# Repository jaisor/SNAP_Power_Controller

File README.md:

# SNAP Power Controller

A small solar charger board for a single-cell (1S) Li-ion/LiPo battery, built for solar-powered LoRa mesh nodes such as [SNAP v1.2](https://makerworld.com/en/models/3360988-snap-v1-2-solar-node-adaptable-platform-2x200ma). Up to four 5V panels feed a CN3791 MPPT buck charger. A switched output powers the node, and an INA3221 reports voltage and current on three channels over I2C.

Designed in KiCad 10.

> **Status:** the schematic is complete and passes ERC. The PCB (52 × 29 mm, 2mm corner chamfers, four M3 mounting holes, two layers) is **placed and routed** with a clean DRC, but hasn't had a manual layout review. A first board has been wired up and tested with a XIAO + Wio-SX1262 on a custom Meshtastic build, and everything seems to work as expected so far, including the I2C sensor. A sunlight test in a real solar node is under way, with the expected voltage and charge current so far. See [Testing](#testing).
>
> **v1.1:** a three-channel INA3221 replaces v1.0's INA219 and its SOLAR/BATT switch, and the board is smaller. v1.1 hasn't been built or tested yet; the test results below are from v1.0 boards with the INA219. See the [change log](CHANGELOG.md).

## Built for solar mesh nodes

This controller is meant for solar mesh nodes like the [SNAP v1.2: Solar Node Adaptable Platform](https://makerworld.com/en/models/3360988-snap-v1-2-solar-node-adaptable-platform-2x200ma). It simplifies their build in three ways:

- **Easy, clean connections:** the panels, battery, node and switches each plug into their own connector.
- **Improved solar charging:** an MPPT charger tuned for 5V panels, with a diode for every panel built into the board.
- **I2C power sensing:** configurable for either the battery or the solar circuit.

I2C power sensors are supported natively by both [Meshtastic](https://meshtastic.org) and [MeshCore](https://github.com/meshcore-dev/MeshCore). In most cases the node recognizes the INA3221 automatically once it's connected.

In the SNAP v1.2 example build, shown below, the board replaces several separately wired parts:

| Example build part | With this board |
|---|---|
| CN3158 MPPT module (SDBK03TA) | CN3791 MPPT buck charger, tuned for 5V panels (VIN held at 4.42V) and charging at 0.8A |
| One 1N5819 per panel, soldered inline | A 1N5819WS per input on the board, for up to four panels |
| Hand-soldered panel, battery and node wiring | Plug-in connectors for every connection: Micro JST 1.25, with 2.54mm pin headers for the switches |
| Latching on/off switch wired into the battery lead | Two switch connectors: SW_BATT cuts the battery, SW_LOAD cuts only the node |
| (none) | INA3221 power monitor on I2C, reading the battery, the total solar input and panel 1 at once |

### Example wiring

| Board connector | Connects to |
|---|---|
| J1, J2 (Solar_5V) | Two [FellDen 5V 200mA 110×60mm panels](https://www.amazon.com/dp/B0BND5NYGK), the ones SNAP v1.2 uses. J3 and J4 take up to two more |
| J5 (BATT) | An 18650 Li-ion cell (1S, 3.0–4.2V) in its holder |
| J8 (SW_LOAD) | The SNAP on/off switch cap's latching button. To cut the battery entirely, use J7 (SW_BATT) as well, or instead |
| J7 / J8 left unswitched | Both switch connectors are in series with the power path, so an unused one needs a 2.54mm jumper cap, or a wire bridging its pads on the back of the board. Otherwise the battery or the node stays disconnected |
| J6 (VOUT) | The XIAO nRF52840's BAT+ / BAT− pads, which is where SNAP powers it from the 18650 today |
| J9 (I2C) | XIAO 3V3 → VCC, D6 → SDA, D7 → SCL, GND → GND, on a 4-wire cable coloured red VCC, black GND, yellow SCL, white SDA. These pins need a Meshtastic build with I2C on D6/D7 (see the table below) |
| JP1 (LED) | Nothing. Bridge it with solder if you want the status LEDs. It's open as supplied, so the LEDs stay dark |

The INA3221 reads the battery's charge and discharge current, what the panels deliver in total, and panel 1 on its own, all at the same time. There's no switch to set.

The XIAO's I2C pins depend on the firmware build. D4 and D5 can't be used with the Wio-SX1262, because the radio uses them.

| Firmware build | SDA | SCL | Status |
|---|---|---|---|
| Meshtastic `seeed_xiao_nrf52840_kit`, custom build with I2C on D6/D7 | D6 | D7 | Tested on this board |
| Meshtastic `seeed_xiao_nrf52840_kit_i2c` | D6 | D7 | From the firmware source, not tested |
| Meshtastic `seeed_xiao_nrf52840_kit`, unmodified (D6/D7 are reserved for the GNSS module) | NFC1 pad (underside) | NFC2 pad (underside) | From the firmware source, not tested |
| MeshCore `Xiao_nrf52` | D7 | D6 | From the firmware source, not tested |

The INA3221 uses address 0x42. Meshtastic also expects the DFRobot Lark weather sensor at 0x42, so the two can't share a bus.

In Meshtastic, enable power metrics in the telemetry settings so the readings are sent to the mesh.

## Features

- **Solar input:** up to four 5V panels in parallel (Micro JST 1.25), each isolated by its own 1N5819WS Schottky (SOD-323) so a shaded or unplugged panel doesn't drag the others down.
- **MPPT charging:** [CN3791](https://naylampmechatronics.com/img/cms/001216/CN3791.PDF) PWM buck charger with constant-voltage MPPT set to 4.42V input. Charges at 0.8A to 4.2V (CC/CV, trickle charge for deeply discharged cells, automatic recharge).
- **Battery and load switching:** connectors for two panel-mount switches. **SW_BATT** disconnects the battery from everything. **SW_LOAD** cuts only the output, so the battery keeps charging.
- **Output:** VOUT connector (Micro JST 1.25) that powers the module from the battery.
- **Reverse-battery protection:** Q2, a P-channel MOSFET between the battery connector and the rest of the board. A cell plugged in backwards is blocked instead of shorting through the charger. With the cell the right way round, Q2 is fully on in both directions, adding about 60mV of drop at 0.8A.
- **Power monitoring:** [INA3221](https://www.ti.com/lit/ds/symlink/ina3221.pdf) at I2C address 0x42, with three channels: the battery (bidirectional current plus voltage), the total solar input, and panel 1 on its own.
- **Status LEDs:** red while charging, green when charging is done. They're powered through JP1, an open solder jumper next to R1 on the top of the board: bridge its two pads with solder to turn them on. Left open, the LEDs are disconnected and draw nothing.

## Schematic

The schematic follows the CN3791 datasheet's typical application circuit (Figure 1), with these changes:

| Item | Value | Why |
|---|---|---|
| Charge current | 0.8A (R5 = 0.15Ω) | I<sub>CH</sub> = 120mV / R5. Leaves margin on the 1.0A-rated connectors; use 0.24Ω for 0.5A with small cells. |
| MPPT setpoint | 4.42V at VIN (R3/R4 = 26.7k/10k) | Chosen for panels that measure about 5.5V open-circuit. It's below the CN3791's specified 4.5V minimum input. Typical parts run down to their 3.8V undervoltage lockout, but the datasheet doesn't guarantee it. With 6V panels, use R3 = 30.1k (4.83V), which stays in spec. V<sub>MPPT</sub> = 1.205V × (1 + R3/R4). The panels sit one diode drop higher (~4.7–4.9V), a little under a cool 5V panel's max-power voltage of about 5.0V. That voltage falls about 0.4% per °C, to about 4.2V at a 65°C cell temperature, and a fixed set point above it cuts the panel's output. Modeled for a 10-cell panel, 4.42V gives 99% of maximum power at 25°C and 84% at 65°C. v1.0's 4.58V (28.0k) gives 100% and 71%. |
| Blocking diode D1 | omitted | The input diodes already stop the battery feeding back into the panels. Leaving D1 out saves ~0.4V of headroom; the trade-off is ~21µA of battery drain in the dark. |
| Inductor | 22µH, Bourns SRN6045TA | Meets the datasheet's L > 5 × (VCC − VBAT) µH, with ~0.2A ripple. |
| Input diodes | 1N5819WS, SOD-323 (40V/1A) | The panels peak at ~200–300mA each, so the SMD part has plenty of margin and saves ~12mm of board width over DO-41. |

## PCB

| Area | Parts |
|---|---|
| Left end | M3 mounting holes H1/H3 in the corners. Between them, the 4-pin I2C connector J9 at the edge and the INA3221 (U2) beside it, with its bypass capacitor C6 and the I2C pull-ups R8/R9 above |
| Left column | Solar inputs J1–J4, each with its 1N5819WS (D5–D8). Panel 1's shunt R10 sits beside J1, with D5 just below it |
| Top middle | Buck power stage in current-flow order: R7, C1/C5, Q1, D2, L1, R5, C3 |
| Middle | CN3791 (U1) with its support parts and status LEDs, and JP1, the LED solder jumper, right of R1 |
| Right middle | Under L1: battery shunt R6 and reverse-battery MOSFET Q2, then VOUT (J6) and battery (J5) |
| Right end | M3 mounting holes H2/H4 in the corners, with the SW_BATT/SW_LOAD switch headers (J7/J8) between them |

Every reference label sits next to its own part, clear of pads, other parts and the edge (DRC reports no silkscreen issues). The holes are plain non-plated 3.2mm M3 holes, 4mm in from each edge.

### Dimensions

The [wiring diagram](#built-for-solar-mesh-nodes) includes a dimension drawing to scale.

| | |
|---|---|
| Outline | 52 × 29mm, with a 2mm × 45° chamfer on each corner |
| Thickness | 1.6mm PCB, two layers. All parts are on the top side; the through-hole connector pins stick out the back |
| Mounting holes | Four, 3.2mm diameter, not plated, for M3 screws |
| Hole positions | One in each corner, centre 4mm from both edges |
| Hole spacing | 44mm across, 21mm down, centre to centre |

**Silkscreen labels:**

- **Connector functions:** `SW_BATT` (J7) and `SW_LOAD` (J8) are printed above the two switch headers. `BATT` (J5) and `VOUT` (J6) are vertical labels to the left of those connectors.
- **Solar inputs:** one `Solar_5V` label, with a bracket along the four solar inputs (J1–J4).
- **Polarity:** `-` and `+` under the solar, battery and VOUT connectors (J1–J6), on the side of the matching pin.
- **I2C connector:** `I2C` under J9 on the front (J9 has no reference label; there's no room for both). The pin names (`VCC`, `GND`, `SCL`, `SDA`) are printed beside its pads on the back.
- **Back:** the module ID, "Solar Charge Module v1.1 / by JaisorGadgets / Nov. 9, 2026".

**Routing** (drawn by hand in `tools/draw-routes.py`, so it comes out the same on every run):

- **Ground:** the bottom layer is a GND plane in one piece, covering about 87% of the board, and the top layer has a GND fill. Every surface-mount GND pad gets its own via down to the plane, and 46 stitching vias on a 3mm grid tie the two pours together.
- **Track widths:** power paths are 0.8mm, 0.4mm into the small diode pads. Signals are 0.25mm, with 0.2mm on the sense lines where they squeeze past pads.
- **Kelvin sensing:** the CN3791's current-sense pins and each INA3221 channel's two inputs connect straight to the pads of their shunt resistors (R5; R6, R7, R10). Each channel's two sense lines run side by side. Channel 3's pair runs over and under J1, channel 2's passes between J2 and J3, and channel 1's follows the bottom edge from the battery shunt to U2.
- **Layer use:** nearly all track is on the top layer: about 454mm, against 25mm on the bottom. The bottom layer only carries short hops: the gate drive under VIN, VIN to R3, the two channel 2 sense lines under the PV bus, and three links under U2.
- **Size:** 212 track segments and 68 vias, 57 of them on GND.
- **Checks:** DRC reports 0 violations and 0 unconnected items, and schematic parity is clean.

Review it before ordering, especially the buck converter's switching loop (C1 → Q1 → D2, which returns through the ground plane).

Still to do: a manual layout review before ordering (see Fabrication).

## Connectors

| Ref | Connector | Pin 1 | Pin 2 | Notes |
|---|---|---|---|---|
| J1–J4 | Micro JST 1.25, 2-pin | Panel + | GND | 5V solar panels, any combination of 1–4 |
| J5 | Micro JST 1.25, 2-pin | Battery + | GND | 1S Li-ion/LiPo, 4.2V |
| J6 | Micro JST 1.25, 2-pin | VOUT | GND | Battery voltage out to the powered module, through SW_LOAD |
| J7 | 2.54mm pin header, 2-pin | VBAT (charger) | BATT+ (battery) | SW_BATT: panel-mount SPST switch, rated ≥1A or the module's peak current |
| J8 | 2.54mm pin header, 2-pin | VBAT | VOUT | SW_LOAD: panel-mount SPST switch, same rating |
| J9 | Micro JST 1.25, 4-pin | VCC (3.3–5V) | GND | Pin 3 = SCL, pin 4 = SDA, matching the common red/black/yellow/white 4-wire cable. VCC comes from the MCU and powers the INA3221. v1.0 boards have SDA on pin 2 and GND on pin 4. |

J1–J6 and J9 are Micro JST 1.25 (Molex PicoBlade-compatible) vertical headers, Molex 53047-0210 (2-pin) and 53047-0410 (4-pin). They mate with standard female cable housings (Molex 51021). J7 and J8 are standard 2.54mm vertical pin headers, which take a 2.54mm female housing or a jumper cap. Notes:

- **Current:** PicoBlade contacts are rated 1.0A. The charge current is set to 0.8A to stay under that on the battery connector (J5). Keep the module's load current under 1A too, since it flows through J5 when the panels are dark.
- **No keying between functions:** J1–J6 are the same 2-pin type, so a battery lead fits a solar socket. Check the silkscreen before plugging in. The switch headers take a different plug, so they can't be mixed up with these.
- **Battery polarity:** "JST 1.25" LiPo pigtails have no standard polarity. Check that red goes to the pin marked `+` (pin 1 on J5) before connecting. Q2 blocks a reversed cell, but fit the cell with SW_BATT off anyway: with SW_BATT on in sunlight, the charger's output can partly turn Q2 on and push a limited current into a reversed cell, which heats Q2.
- **Reading the marks:** pin 1 is `+` on J1–J6. J1–J4 are rotated 180° from J5 and J6, so the marks read `- J1 +` on the solar inputs and `+ J5 -` on the right-hand connectors.

**Operating note:** if SW_BATT is off while the panels are in sun, the charger sees no battery and VBAT pulses around 4.2V. Keep SW_LOAD off in that state.

## Power monitor (INA3221)

- **Address:** 0x42 (A0 = SDA). That's the INA3221 default in both Meshtastic and MeshCore.
- **Shunts:** all three are 0.1Ω, which both firmwares assume. Full scale is ±163.8mV, so about ±1.64A, in 0.4mA steps.
- **Pull-ups:** R8/R9 are 10k I2C pull-ups to the MCU's VCC. Leave them off if the MCU board already has pull-ups.

| Channel | Shunt | Current | Bus voltage |
|---|---|---|---|
| 1 | R6, between BATT+ and the cell | Positive while charging, negative while discharging | Cell voltage, readable even with SW_BATT off. It's measured after Q2, so it reads up to about 50mV off while current flows |
| 2 | R7, between the PV bus and VIN | Total solar current, always ≥ 0 | VIN (panel voltage minus the diode drop) |
| 3 | R10, between J1 and its diode D5 | Panel 1's current, always ≥ 0 | Panel 1's own voltage, before its diode |

Channel 3 shows where panel 1 actually operates, which is the number to compare against the panel's maximum-power voltage when tuning the MPPT set point.

**Firmware support** (checked in the source code on 2026-11-09, not yet on hardware):
- **Meshtastic:** looks for an INA3221 at 0x42. It reports all three channels' voltage and current as power metrics, and uses channel 1 as the battery by default.
- **MeshCore:** the XIAO nRF52 build includes INA3221 support (`ENV_INCLUDE_INA3221`). It reports voltage, current and power for each channel.

## Testing

| Test | Setup | Status |
|---|---|---|
| First power-up | Board wired to a XIAO + Wio-SX1262, running Meshtastic built from `seeed_xiao_nrf52840_kit` with I2C on D6/D7 | Done. Everything seems to work as expected, including the INA219 over I2C |
| INA219 battery current | Same setup, battery at about 4V | Done. Discharging: about −12 to −15mA. Charging from the XIAO's USB: +100mA |
| Sunlight | Board wired into a real solar node with 4 × 60mA panels, with metrics tracked in Grafana dashboards | In progress. Voltage and charge current rose as expected when exposed to sunlight. One reading in the Meshtastic app: 4.56V, 110.5mA |

The signs match the expected convention: positive while charging, negative while discharging. The USB reading comes from the XIAO's own charger, so it doesn't test the CN3791. The sunlight reading is from SW3's SOLAR position: 4.56V is above a Li-ion cell's 4.2V and close to the 4.58V MPPT set point of the board tested (v1.1 lowers it to 4.42V). It's a single reading, and longer-term results are still to come. These tests used a board with Micro JST 1.25 connectors on J7 and J8, so the pin-header version hasn't been built yet. In the sunlight test build, J7 and J8 are bridged with wire on the back of the board, so neither switch is fitted.

## Safety

This is an experimental design for charging a lithium-ion cell. It's provided as is, with no warranty, and hasn't been certified to any safety standard. If you build it, you're responsible for:

- Assembling it correctly and checking connector polarity before connecting a cell. J1–J6 share one connector type, so a lead plugs into the wrong socket easily. Q2 protects against a reversed cell on J5, but not against every fault, such as a battery plugged into a solar input.
- Using a protected cell or a separate protection circuit. The CN3791 charges the cell but doesn't protect it from over-discharge or short circuits.
- Fusing, wiring and an enclosure suited to where the node is installed, including outdoor heat and moisture.
- Not using it where a failure could hurt someone or damage property.

## Fabrication

Download the package from the [latest release](https://github.com/jaisor/SNAP_Power_Controller/releases/latest). That release is v1.1, the design in this repo; the [change log](CHANGELOG.md) lists what changed since v1.0. The package is generated into `output/fab/`, which isn't tracked in git:

| File | Contents |
|---|---|
| `SolarChargeModule_v1.1_gerbers.zip` | Upload this to the board house. 9 Gerber X2 layers (copper, mask, paste and silkscreen on both sides, plus the outline), a Gerber job file, plated and non-plated Excellon drill files, and drill maps |
| `FAB_NOTES.txt` | Order settings: 2 layers, FR-4 1.6mm, 1oz copper, 52 × 29mm, 0.2mm/0.2mm minimum track/space, 0.3mm minimum drill, tented vias, four 3.2mm non-plated holes. Also assembly cautions |
| `SolarChargeModule_v1.1_BOM.csv` | BOM in JLCPCB format (Comment, Designator, Footprint, LCSC Part #), plus a Manufacturer Part column for the specific parts |
| `SolarChargeModule_v1.1_CPL.csv` | Pick-and-place file for top-side assembly, in the same coordinates as the Gerbers |

LCSC part numbers are only filled in where verified (D5–D8). Pick the rest in the assembler's part search, and check rotation and polarity in their preview. The PicoBlade headers and the J7 and J8 pin headers are through-hole parts. JP1 is a solder jumper made of bare pads, so it has no part to place.

Regenerating the package (after the board is final and DRC is clean):

```bash
OUT=output/fab
P=SNAP_Power_Controller
kicad-cli pcb export gerbers --layers F.Cu,B.Cu,F.Paste,B.Paste,F.Silkscreen,B.Silkscreen,F.Mask,B.Mask,Edge.Cuts --subtract-soldermask --check-zones -o $OUT/gerbers $P.kicad_pcb
kicad-cli pcb export drill --format excellon --excellon-units mm --excellon-zeros-format decimal --drill-origin absolute --excellon-separate-th --generate-map --map-format gerberx2 -o $OUT/gerbers/ $P.kicad_pcb
kicad-cli pcb export pos --format csv --units mm --side both -o $OUT/pos-kicad.csv $P.kicad_pcb
kicad-cli sch export bom --fields 'Value,Reference,Footprint,${QUANTITY}' --labels 'Comment,Designator,Footprint,Qty' --group-by 'Value,Footprint' --ref-range-delimiter '' --exclude-dnp -o $OUT/bom-kicad.csv $P.kicad_sch
node tools/fab-package.js $OUT
```

## Repository layout

```
SNAP_Power_Controller.kicad_pro / .kicad_sch / .kicad_pcb   KiCad project
SolarNode.kicad_sym             project symbol library (CN3791)
sym-lib-table
tools/
  gen-schematic.js              generates the schematic (Node)
  place-pcb.py                  places footprints, labels, holes, outline (KiCad Python / pcbnew)
  draw-routes.py                draws the tracks, vias and GND pours from fixed coordinates (run after place-pcb.py)
  route-pcb.py                  the earlier auto-router, kept for reference (v1.0's copper came from it)
  make-diagram.py               draws docs/images/wiring-diagram.png from the board render
  fab-package.js                JLCPCB-style BOM/CPL, fab notes and Gerber zip from the kicad-cli exports
docs/images/                    images used in this README (snap/: photos from the SNAP v1.2 MakerWorld post)
CLAUDE.md                       design decisions and working notes
LICENSE                         CERN-OHL-P-2.0 (hardware design and documentation)
tools/LICENSE                   MIT (scripts)
```

The schematic and the board layout are generated by scripts in `tools/`, and checked with `kicad-cli` ERC/DRC (including schematic parity). See [CLAUDE.md](CLAUDE.md) for the full design rationale and workflow. Generated outputs (`output/`: BOM, reports, fab files) are not tracked.

## Regenerating the design

The whole design can be rebuilt from the scripts. Run these from the repo root, with `kicad-cli` from KiCad 10:

```bash
# 1. Schematic (Node): rewrites the .kicad_sch, SolarNode.kicad_sym and sym-lib-table
node tools/gen-schematic.js
kicad-cli sch erc --format json --severity-all -o erc.json SNAP_Power_Controller.kicad_sch
# 2. Netlist for the board scripts
kicad-cli sch export netlist --format kicadxml -o net.xml SNAP_Power_Controller.kicad_sch
# 3. Board (KiCad's Python): placement + labels + holes + outline, then tracks + GND pours
"C:/Program Files/KiCad/10.0/bin/python.exe" tools/place-pcb.py net.xml
"C:/Program Files/KiCad/10.0/bin/python.exe" tools/draw-routes.py
# 4. Check: expect 0 violations, 0 unconnected, 0 parity issues
kicad-cli pcb drc --schematic-parity --severity-all --format json -o drc.json SNAP_Power_Controller.kicad_pcb
```

The scripts overwrite their output files. Once you edit the schematic or board in KiCad, stop regenerating that file (or port your edits into the scripts first).

Refreshing the images in `docs/images/`:

```bash
kicad-cli sch export svg -o docs/images SNAP_Power_Controller.kicad_sch
kicad-cli pcb render --side top --width 1600 --height 900 --quality high --zoom 1.6 -o docs/images/pcb-top.png SNAP_Power_Controller.kicad_pcb
kicad-cli pcb render --side bottom --width 1600 --height 900 --quality high --zoom 1.6 -o docs/images/pcb-bottom.png SNAP_Power_Controller.kicad_pcb
kicad-cli pcb render --width 1600 --height 1000 --quality high --perspective --rotate "-40,0,-25" -o docs/images/pcb-iso.png SNAP_Power_Controller.kicad_pcb
```

(The schematic export is named `SNAP_Power_Controller.svg`; rename it to `schematic.svg`.)

After refreshing `pcb-top.png`, redraw the wiring diagram with KiCad's Python, which includes Pillow and NumPy:

```bash
"C:/Program Files/KiCad/10.0/bin/python.exe" tools/make-diagram.py
```

## License

Copyright 2026 Jordan Marinov (JaisorGadgets).

The hardware design (schematic, board, symbol library) and its documentation, including the images in `docs/images/`, are licensed under the [CERN Open Hardware Licence Version 2 – Permissive](LICENSE) (CERN-OHL-P-2.0). You may redistribute and modify them, and make and sell products from them, under the terms of the licence. They are distributed WITHOUT ANY EXPRESS OR IMPLIED WARRANTY, INCLUDING OF MERCHANTABILITY, SATISFACTORY QUALITY AND FITNESS FOR A PARTICULAR PURPOSE. See section 5 of the licence for the disclaimer and limitation of liability.

The scripts in `tools/` are licensed under the [MIT License](tools/LICENSE).

Source location: https://github.com/jaisor/SNAP_Power_Controller

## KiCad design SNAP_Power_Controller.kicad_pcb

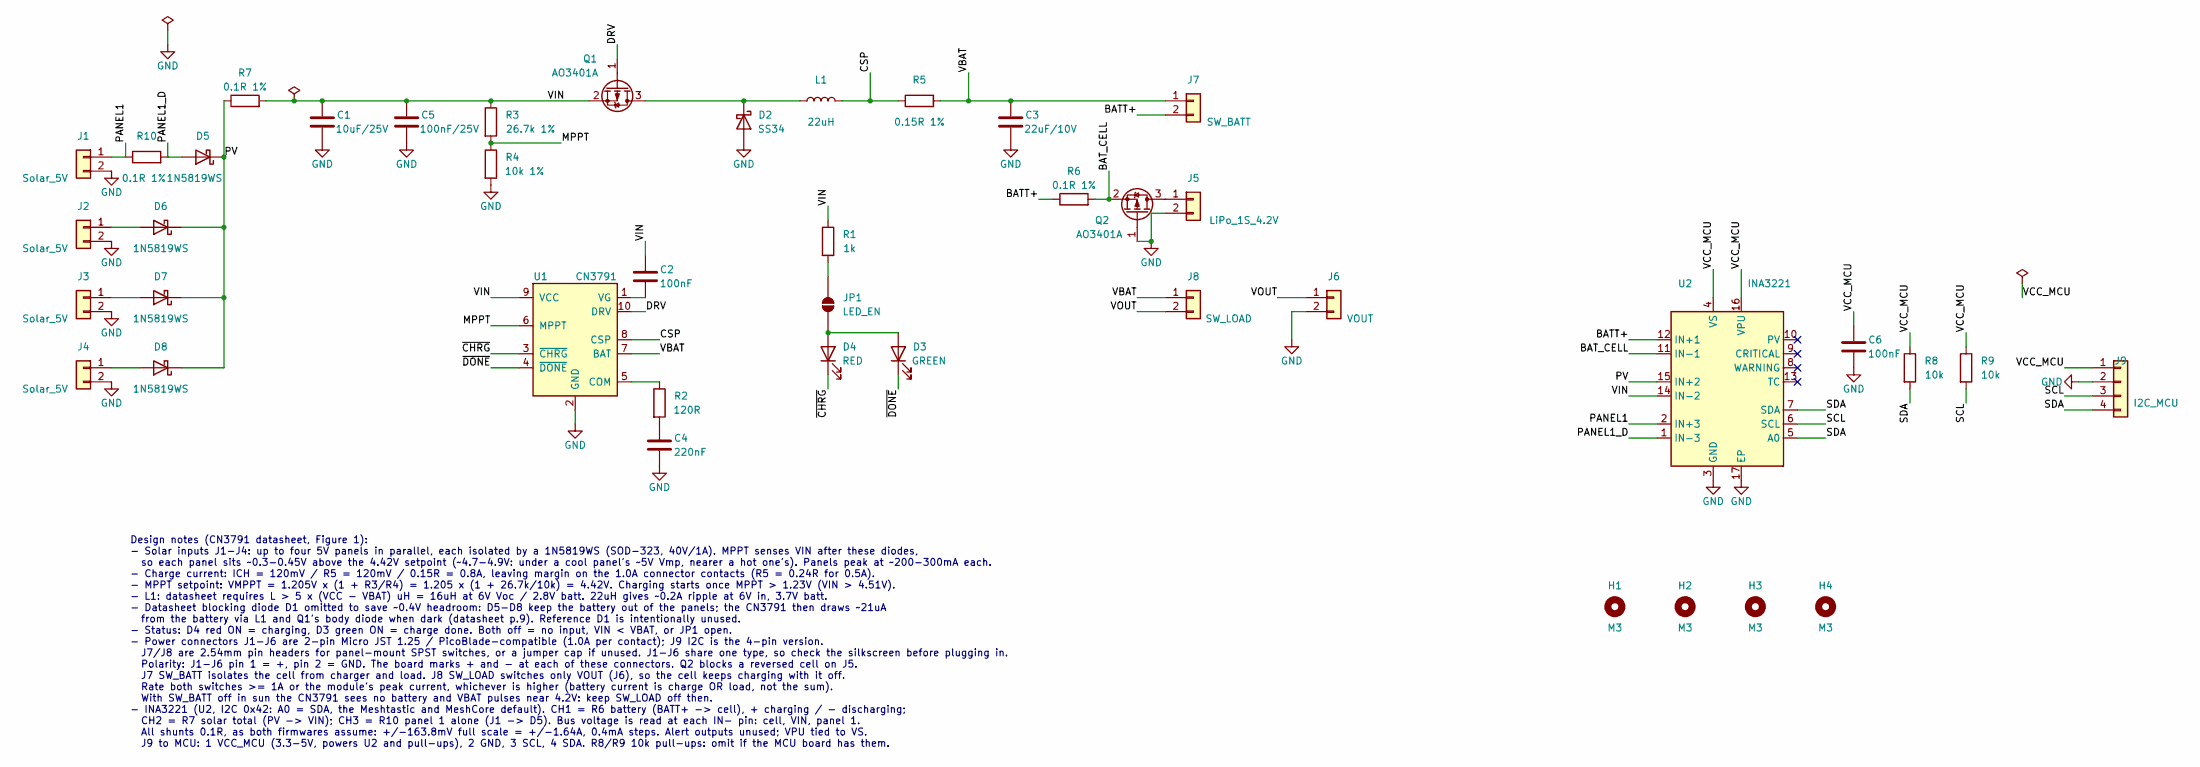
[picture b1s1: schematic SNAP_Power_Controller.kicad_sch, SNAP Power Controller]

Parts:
C1: 10uF/25V; C_1206_3216Metric
C2, C6: 100nF; C_0603_1608Metric
C3: 22uF/10V; C_1206_3216Metric
C4: 220nF; C_0603_1608Metric
C5: 100nF/25V; C_0603_1608Metric
D2: SS34; D_SMA
D3: GREEN; LED_0603_1608Metric
D4: RED; LED_0603_1608Metric
D5, D6, D7, D8: 1N5819WS; D_SOD-323
H1, H2, H3, H4: M3; MountingHole_3.2mm_M3
J1, J2, J3, J4: Solar_5V; Molex_PicoBlade_53047-0210_1x02_P1.25mm_Vertical
J5: LiPo_1S_4.2V; Molex_PicoBlade_53047-0210_1x02_P1.25mm_Vertical
J6: VOUT; Molex_PicoBlade_53047-0210_1x02_P1.25mm_Vertical
J7: SW_BATT; PinHeader_1x02_P2.54mm_Vertical
J8: SW_LOAD; PinHeader_1x02_P2.54mm_Vertical
J9: I2C_MCU; Molex_PicoBlade_53047-0410_1x04_P1.25mm_Vertical
JP1: LED_EN; SolderJumper-2_P1.3mm_Open_RoundedPad1.0x1.5mm
L1: 22uH; L_Bourns_SRN6045TA
Q1, Q2: AO3401A; SOT-23
R1: 1k; R_0603_1608Metric
R2: 120R; R_0603_1608Metric
R3: 26.7k 1%; R_0603_1608Metric
R4: 10k 1%; R_0603_1608Metric
R5: 0.15R 1%; R_1206_3216Metric
R6, R7: 0.1R 1%; R_1206_3216Metric
R8, R9: 10k; R_0603_1608Metric
R10: 0.1R 1%; R_0603_1608Metric
U1: CN3791; SSOP-10_3.9x4.9mm_P1.00mm
U2: INA3221; Texas_RGV0016A_VQFN-16-1EP_4x4mm_P0.65mm_EP2.1x2.1mm

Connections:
/BATT+: J7.2, R6.1, U2.12 (IN+1)
/BAT_CELL: Q2.2 (S), R6.2, U2.11 (IN-1)
/CSP: L1.2, R5.1, U1.8 (CSP)
/DRV: Q1.1 (G), U1.10 (DRV)
/MPPT: R3.2, R4.1, U1.6 (MPPT)
/PANEL1: J1.1, R10.1, U2.2 (IN+3)
/PANEL1_D: D5.2 (A), R10.2, U2.1 (IN-3)
/PV: D5.1 (K), D6.1 (K), D7.1 (K), D8.1 (K), R7.1, U2.15 (IN+2)
/SCL: J9.3, R9.2, U2.6 (SCL)
/SDA: J9.4, R8.2, U2.5 (A0), U2.7 (SDA)
/VBAT: C3.1, J7.1, J8.1, R5.2, U1.7 (BAT)
/VCC_MCU: C6.1, J9.1, R8.1, R9.1, U2.4 (VS), U2.16 (VPU)
/VIN: C1.1, C2.1, C5.1, Q1.2 (S), R1.1, R3.1, R7.2, U1.9 (VCC), U2.14 (IN-2)
/VOUT: J6.1, J8.2
/~CHRG: D4.1 (K), U1.3 (~CHRG)
/~DONE: D3.1 (K), U1.4 (~DONE)
GND: C1.2, C3.2, C4.2, C5.2, C6.2, D2.2 (A), J1.2, J2.2, J3.2, J4.2, J5.2, J6.2, J9.2, Q2.1 (G), R4.2, U1.2 (GND), U2.3 (GND), U2.17 (EP)
unnamed: C4.1, R2.2
unnamed: D2.1 (K), L1.1, Q1.3 (D)
unnamed: D3.2 (A), D4.2 (A), JP1.1 (A)
unnamed: D6.2 (A), J2.1
unnamed: D7.2 (A), J3.1
unnamed: D8.2 (A), J4.1
unnamed: J5.1, Q2.3 (D)
unnamed: JP1.2 (B), R1.2
unnamed: R2.1, U1.5 (COM)
unnamed: C2.2, U1.1 (VG)

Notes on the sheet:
Design notes (CN3791 datasheet, Figure 1): - Solar inputs J1-J4: up to four 5V panels in parallel, each isolated by a 1N5819WS (SOD-323, 40V/1A). MPPT senses VIN after these diodes, so each panel sits ~0.3-0.45V above the 4.42V setpoint (~4.7-4.9V: under a cool panel's ~5V Vmp, nearer a hot one's).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

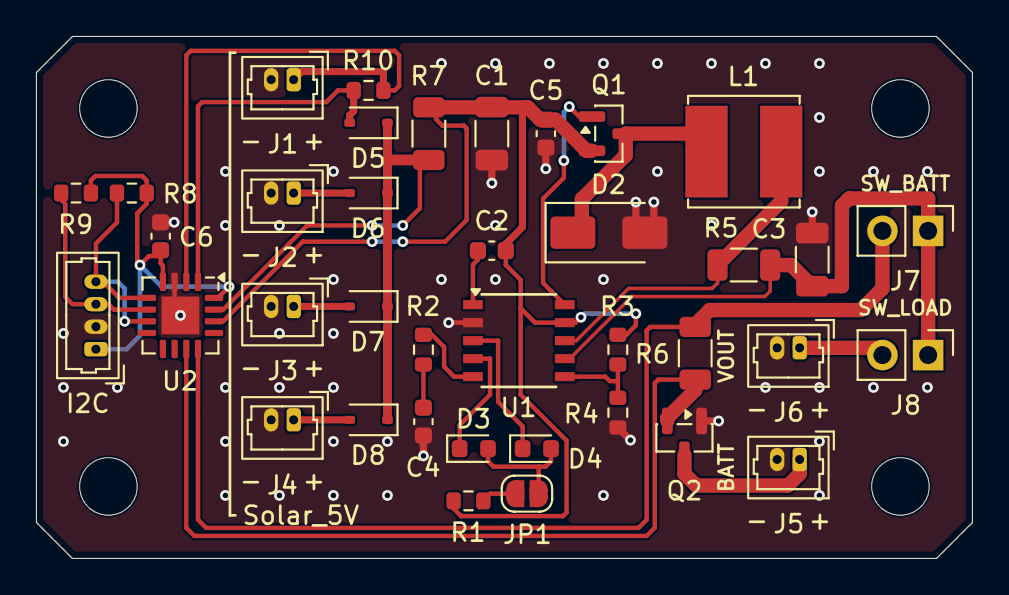
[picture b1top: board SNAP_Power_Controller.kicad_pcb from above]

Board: 2 copper layers, 52.0 x 29.0 mm, 42 parts (0 on the bottom side), 27 nets.
